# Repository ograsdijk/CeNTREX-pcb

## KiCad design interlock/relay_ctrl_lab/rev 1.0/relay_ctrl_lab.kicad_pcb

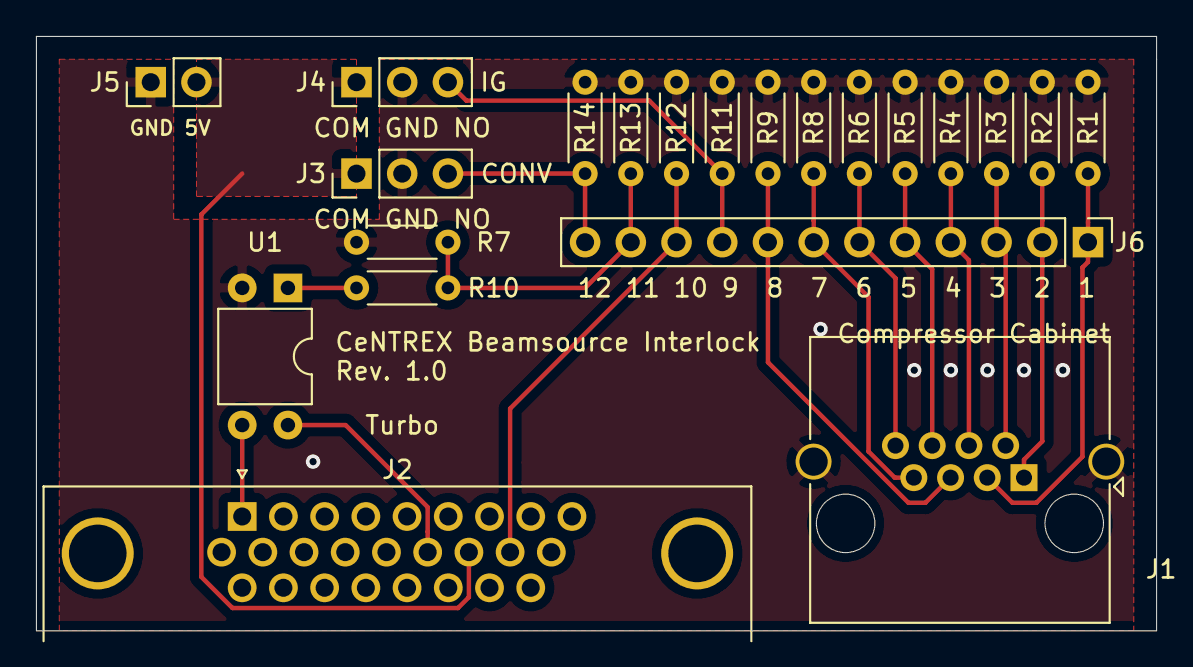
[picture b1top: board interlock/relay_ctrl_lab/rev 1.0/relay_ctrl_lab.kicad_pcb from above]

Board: 2 copper layers, 62.2 x 33.0 mm, 21 parts (0 on the bottom side), 17 nets.

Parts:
J1: RJ45_Shielded; RJ45_Amphenol_RJHSE5380
J2: Conn_01x26; DSUB-26-HD_Male_Horizontal_P2.29x1.98mm_EdgePinOffset3.03mm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
J3, J4: Conn_01x03; PinHeader_1x03_P2.54mm_Vertical
J5: Conn_01x02; PinHeader_1x02_P2.54mm_Vertical
J6: Conn_01x12; PinHeader_1x12_P2.54mm_Vertical
R1, R2, R3, R4, R5, R6, R8, R9, R11, R12, R13, R14: R; R_Axial_DIN0204_L3.6mm_D1.6mm_P5.08mm_Horizontal
R7: 10k; R_Axial_DIN0204_L3.6mm_D1.6mm_P5.08mm_Horizontal
R10: 1.2k; R_Axial_DIN0204_L3.6mm_D1.6mm_P5.08mm_Horizontal
U1: TLP222A; DIP-4_W7.62mm

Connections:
+5V: J2.16, J3.1, J4.1, J5.2
Backing1_active: J1.3, J6.1, R1.1
Backing1_interlock: J1.7, J6.7, R8.1
Backing2_active: J1.4, J6.4, R4.1
Backing2_interlock: J1.8, J6.6, R6.1
Compressor1_active: J1.1, J6.2, R2.1
Compressor1_interlock: J1.5, J6.8, R9.1
Compressor2_active: J1.2, J6.3, R3.1
Compressor2_interlock: J1.6, J6.5, R5.1
Convection_relay: J3.3, J6.12, R14.1
GND: J1.SH, J3.2, J4.2, J5.1, R1.2, R2.2, R3.2, R4.2, R5.2, R6.2, R7.2, R8.2, R9.2, R11.2, R12.2, R13.2, R14.2, U1.2
IG_relay: J4.3, J6.9, R11.1
unnamed: R10.2, U1.1
Turbo_Vref: J2.1, U1.3
Turbo_active: J2.17, J6.10, R12.1
Turbo_interlock: J6.11, R7.1, R10.1, R13.1
Turbo_remotepriority: J2.15, U1.4

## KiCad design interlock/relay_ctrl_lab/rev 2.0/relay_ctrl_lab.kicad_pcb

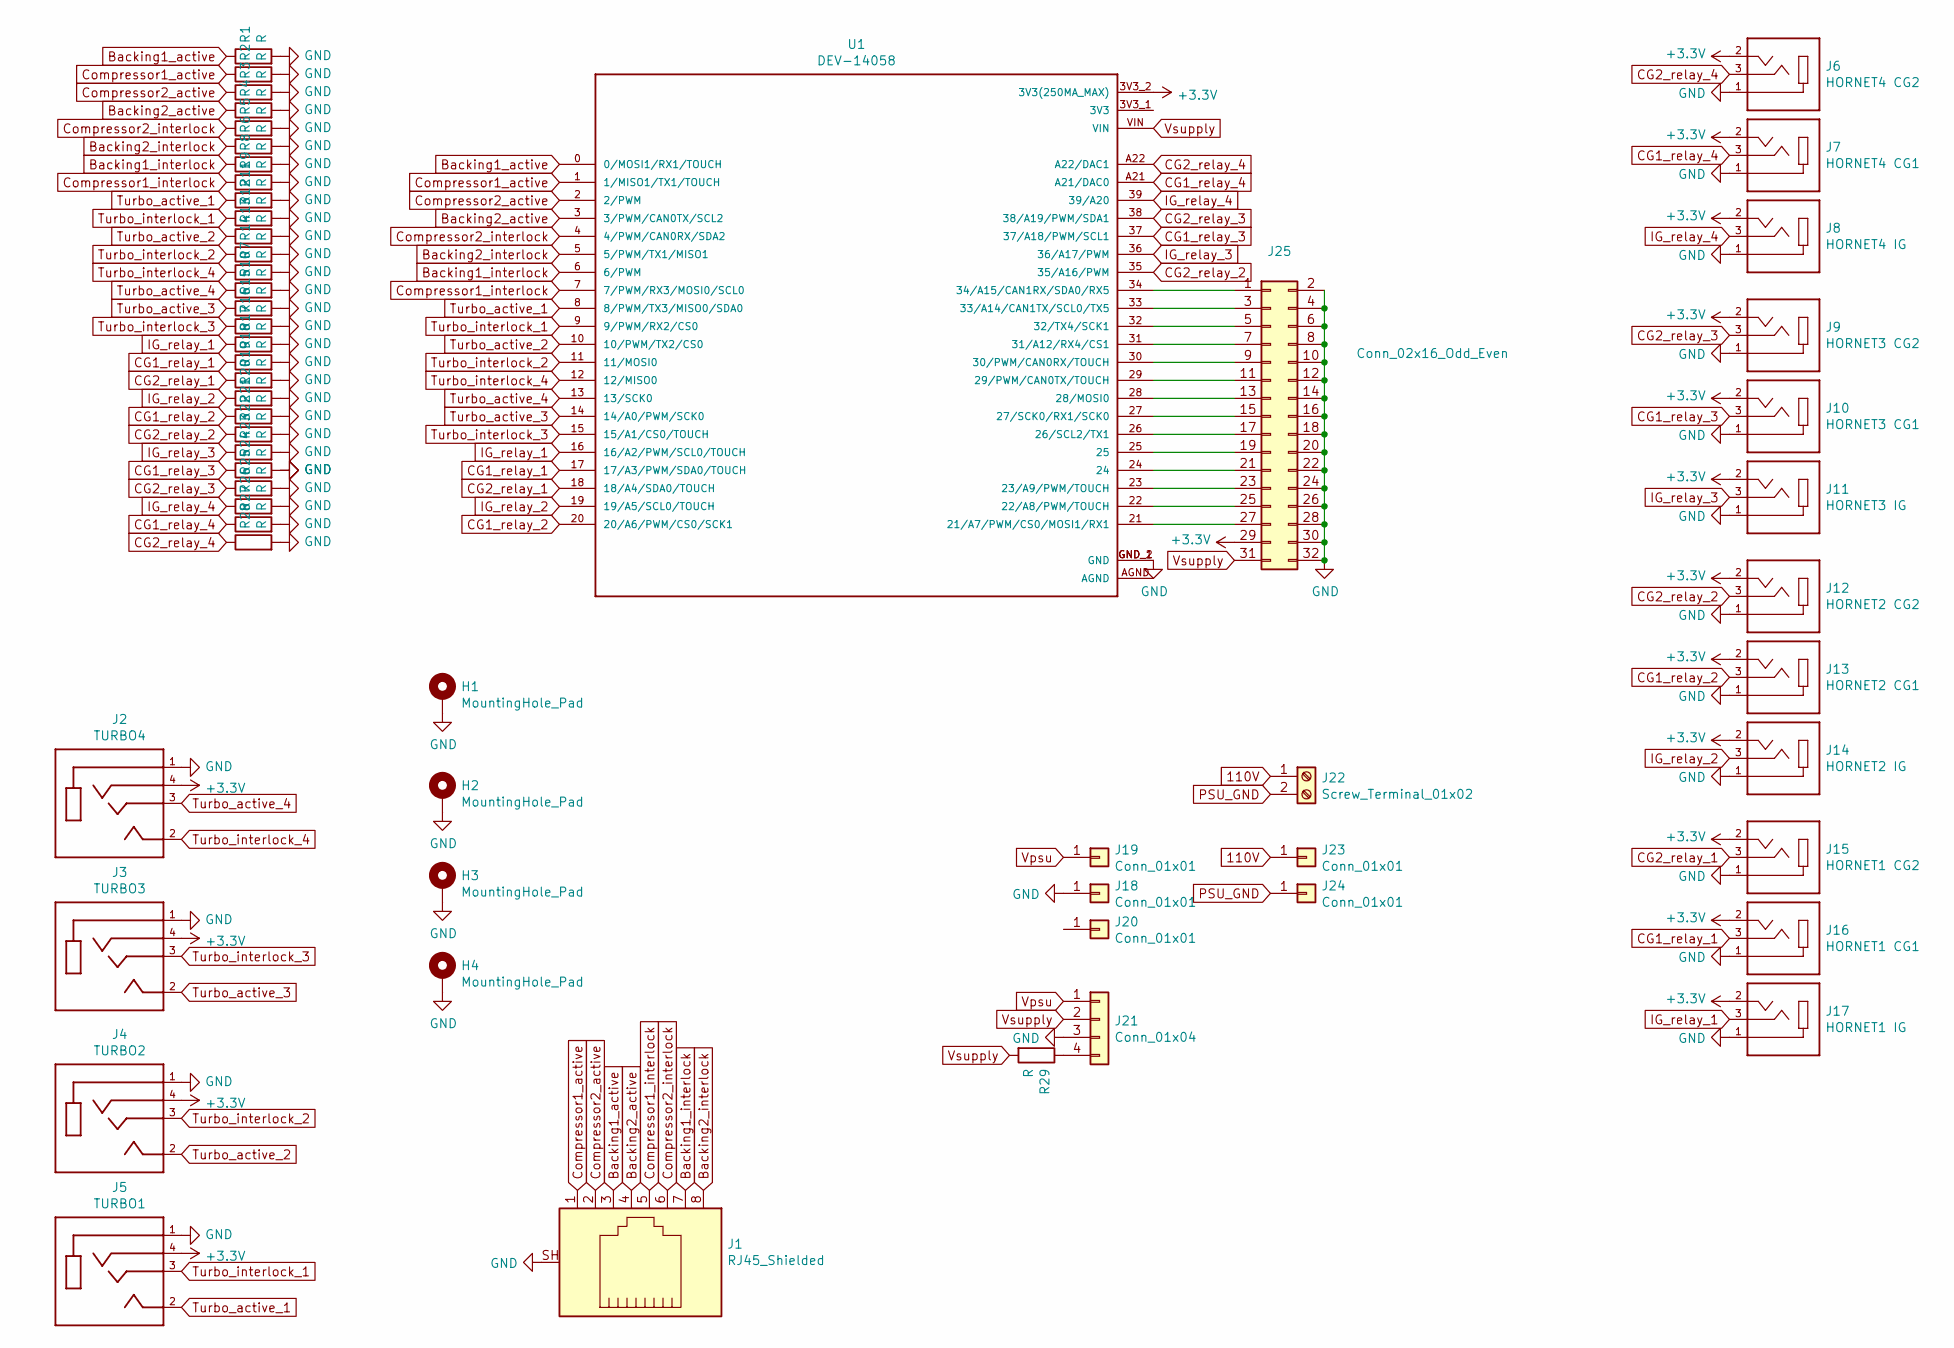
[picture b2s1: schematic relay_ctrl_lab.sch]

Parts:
H1, H2, H3, H4: MountingHole_Pad; MountingHole_3.2mm_M3_DIN965_Pad
J1: RJ45_Shielded; RJ45_Amphenol_RJHSE5380
J2: TURBO4; CUI_SJ-43514-SMT
J3: TURBO3; CUI_SJ-43514-SMT
J4: TURBO2; CUI_SJ-43514-SMT
J5: TURBO1; CUI_SJ-43514-SMT
J6: HORNET4 CG2; CUI_SJ-3523-SMT-TR
J7: HORNET4 CG1; CUI_SJ-3523-SMT-TR
J8: HORNET4 IG; CUI_SJ-3523-SMT-TR
J9: HORNET3 CG2; CUI_SJ-3523-SMT-TR
J10: HORNET3 CG1; CUI_SJ-3523-SMT-TR
J11: HORNET3 IG; CUI_SJ-3523-SMT-TR
J12: HORNET2 CG2; CUI_SJ-3523-SMT-TR
J13: HORNET2 CG1; CUI_SJ-3523-SMT-TR
J14: HORNET2 IG; CUI_SJ-3523-SMT-TR
J15: HORNET1 CG2; CUI_SJ-3523-SMT-TR
J16: HORNET1 CG1; CUI_SJ-3523-SMT-TR
J17: HORNET1 IG; CUI_SJ-3523-SMT-TR
J18, J19, J20, J23, J24: Conn_01x01; PinHeader_1x01_P2.54mm_Vertical
J21: Conn_01x04; PinHeader_1x04_P2.54mm_Vertical
J22: Screw_Terminal_01x02; TerminalBlock_RND_205-00001_1x02_P5.00mm_Horizontal
J25: Conn_02x16_Odd_Even; PinHeader_2x16_P2.54mm_Vertical
R1, R2, R3, R4, R5, R6, R7, R8, R9, R10, R11, R12, R13, R14, R15, R16, R17, R18, R19, R20, R21, R22, R23, R24, R25, R26, R27, R28, R29: R; R_Axial_DIN0204_L3.6mm_D1.6mm_P5.08mm_Horizontal
U1: DEV-14058; SPARKFUN_DEV-14058

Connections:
110V: J22.1, J23.1
+3V3: J2.4 (RING2), J3.4 (RING2), J4.4 (RING2), J5.4 (RING2), J6.2, J7.2, J8.2, J9.2, J10.2, J11.2, J12.2, J13.2, J14.2, J15.2, J16.2, J17.2, J25.29, U1.3V3_2 (3V3(250MA_MAX))
Backing1_active: J1.3, R1.1, U1.0 (0/MOSI1/RX1/TOUCH)
Backing1_interlock: J1.7, R8.1, U1.6 (6/PWM)
Backing2_active: J1.4, R4.1, U1.3 (3/PWM/CAN0TX/SCL2)
Backing2_interlock: J1.8, R6.1, U1.5 (5/PWM/TX1/MISO1)
CG1_relay_1: J16.3, R18.1, U1.17 (17/A3/PWM/SDA0/TOUCH)
CG1_relay_2: J13.3, R21.1, U1.20 (20/A6/PWM/CS0/SCK1)
CG1_relay_3: J10.3, R24.1, U1.37 (37/A18/PWM/SCL1)
CG1_relay_4: J7.3, R27.1, U1.A21 (A21/DAC0)
CG2_relay_1: J15.3, R19.1, U1.18 (18/A4/SDA0/TOUCH)
CG2_relay_2: J12.3, R22.1, U1.35 (35/A16/PWM)
CG2_relay_3: J9.3, R25.1, U1.38 (38/A19/PWM/SDA1)
CG2_relay_4: J6.3, R28.1, U1.A22 (A22/DAC1)
Compressor1_active: J1.1, R2.1, U1.1 (1/MISO1/TX1/TOUCH)
Compressor1_interlock: J1.5, R9.1, U1.7 (7/PWM/RX3/MOSI0/SCL0)
Compressor2_active: J1.2, R3.1, U1.2 (2/PWM)
Compressor2_interlock: J1.6, R5.1, U1.4 (4/PWM/CAN0RX/SDA2)
GND: H1.1, H2.1, H3.1, H4.1, J1.SH, J2.1 (SLEEVE), J3.1 (SLEEVE), J4.1 (SLEEVE), J5.1 (SLEEVE), J6.1, J7.1, J8.1, J9.1, J10.1, J11.1, J12.1, J13.1, J14.1, J15.1, J16.1, J17.1, J18.1, J21.3, J25.2, J25.4, J25.6, J25.8, J25.10, J25.12, J25.14, J25.16, J25.18, J25.20, J25.22, J25.24, J25.26, J25.28, J25.30, J25.32, R1.2, R2.2, R3.2, R4.2, R5.2, R6.2, R7.2, R8.2, R9.2, R10.2, R11.2, R12.2, R13.2, R14.2, R15.2, R16.2, R17.2, R18.2, R19.2, R20.2, R21.2, R22.2, R23.2, R24.2, R25.2, R26.2, R27.2, R28.2, U1.GND_1 (GND), U1.GND_2 (GND)
IG_relay_1: J17.3, R17.1, U1.16 (16/A2/PWM/SCL0/TOUCH)
IG_relay_2: J14.3, R20.1, U1.19 (19/A5/SCL0/TOUCH)
IG_relay_3: J11.3, R23.1, U1.36 (36/A17/PWM)
IG_relay_4: J8.3, R26.1, U1.39 (39/A20)
unnamed: J21.4, R29.1
unnamed: J25.1, U1.34 (34/A15/CAN1RX/SDA0/RX5)
unnamed: J25.3, U1.33 (33/A14/CAN1TX/SCL0/TX5)
unnamed: J25.5, U1.32 (32/TX4/SCK1)
unnamed: J25.7, U1.31 (31/A12/RX4/CS1)
unnamed: J25.9, U1.30 (30/PWM/CAN0RX/TOUCH)
unnamed: J25.11, U1.29 (29/PWM/CAN0TX/TOUCH)
unnamed: J25.13, U1.28 (28/MOSI0)
unnamed: J25.15, U1.27 (27/SCK0/RX1/SCK0)
unnamed: J25.17, U1.26 (26/SCL2/TX1)
unnamed: J25.19, U1.25
unnamed: J25.21, U1.24
unnamed: J25.23, U1.23 (23/A9/PWM/TOUCH)
unnamed: J25.25, U1.22 (22/A8/PWM/TOUCH)
unnamed: J25.27, U1.21 (21/A7/PWM/CS0/MOSI1/RX1)
PSU_GND: J22.2, J24.1
Turbo_active_1: J5.2 (TIP), R11.1, U1.8 (8/PWM/TX3/MISO0/SDA0)
Turbo_active_2: J4.2 (TIP), R13.1, U1.10 (10/PWM/TX2/CS0)
Turbo_active_3: J3.2 (TIP), R15.1, U1.14 (14/A0/PWM/SCK0)
Turbo_active_4: J2.3 (RING1), R10.1, U1.13 (13/SCK0)
Turbo_interlock_1: J5.3 (RING1), R12.1, U1.9 (9/PWM/RX2/CS0)
Turbo_interlock_2: J4.3 (RING1), R14.1, U1.11 (11/MOSI0)
Turbo_interlock_3: J3.3 (RING1), R16.1, U1.15 (15/A1/CS0/TOUCH)
Turbo_interlock_4: J2.2 (TIP), R7.1, U1.12 (12/MISO0)
Vpsu: J19.1, J21.1
Vsupply: J21.2, J25.31, R29.2, U1.VIN

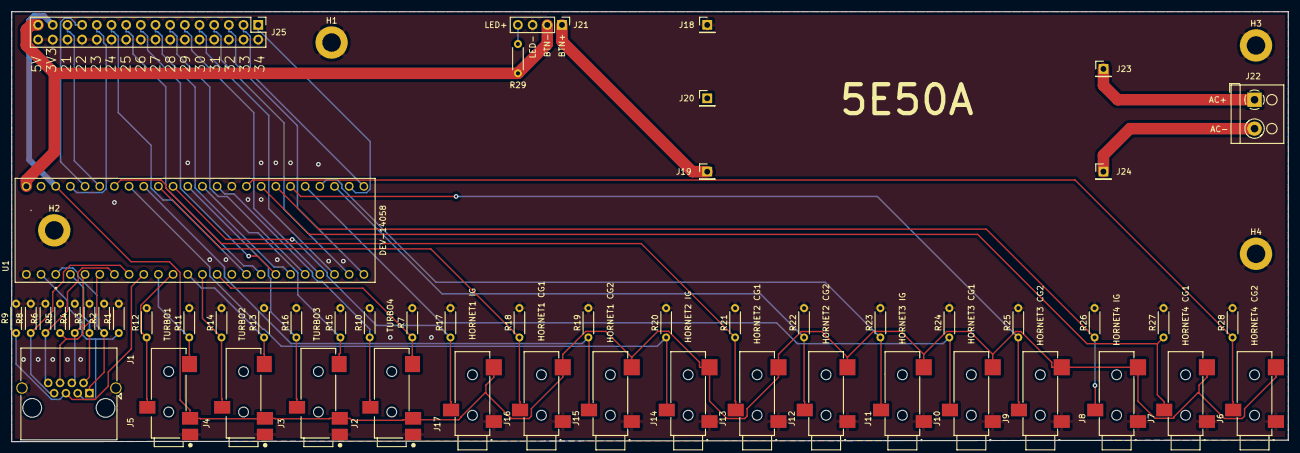
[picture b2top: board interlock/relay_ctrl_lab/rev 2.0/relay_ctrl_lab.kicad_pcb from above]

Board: 2 copper layers, 221.0 x 74.4 mm, 59 parts (0 on the bottom side), 49 nets.

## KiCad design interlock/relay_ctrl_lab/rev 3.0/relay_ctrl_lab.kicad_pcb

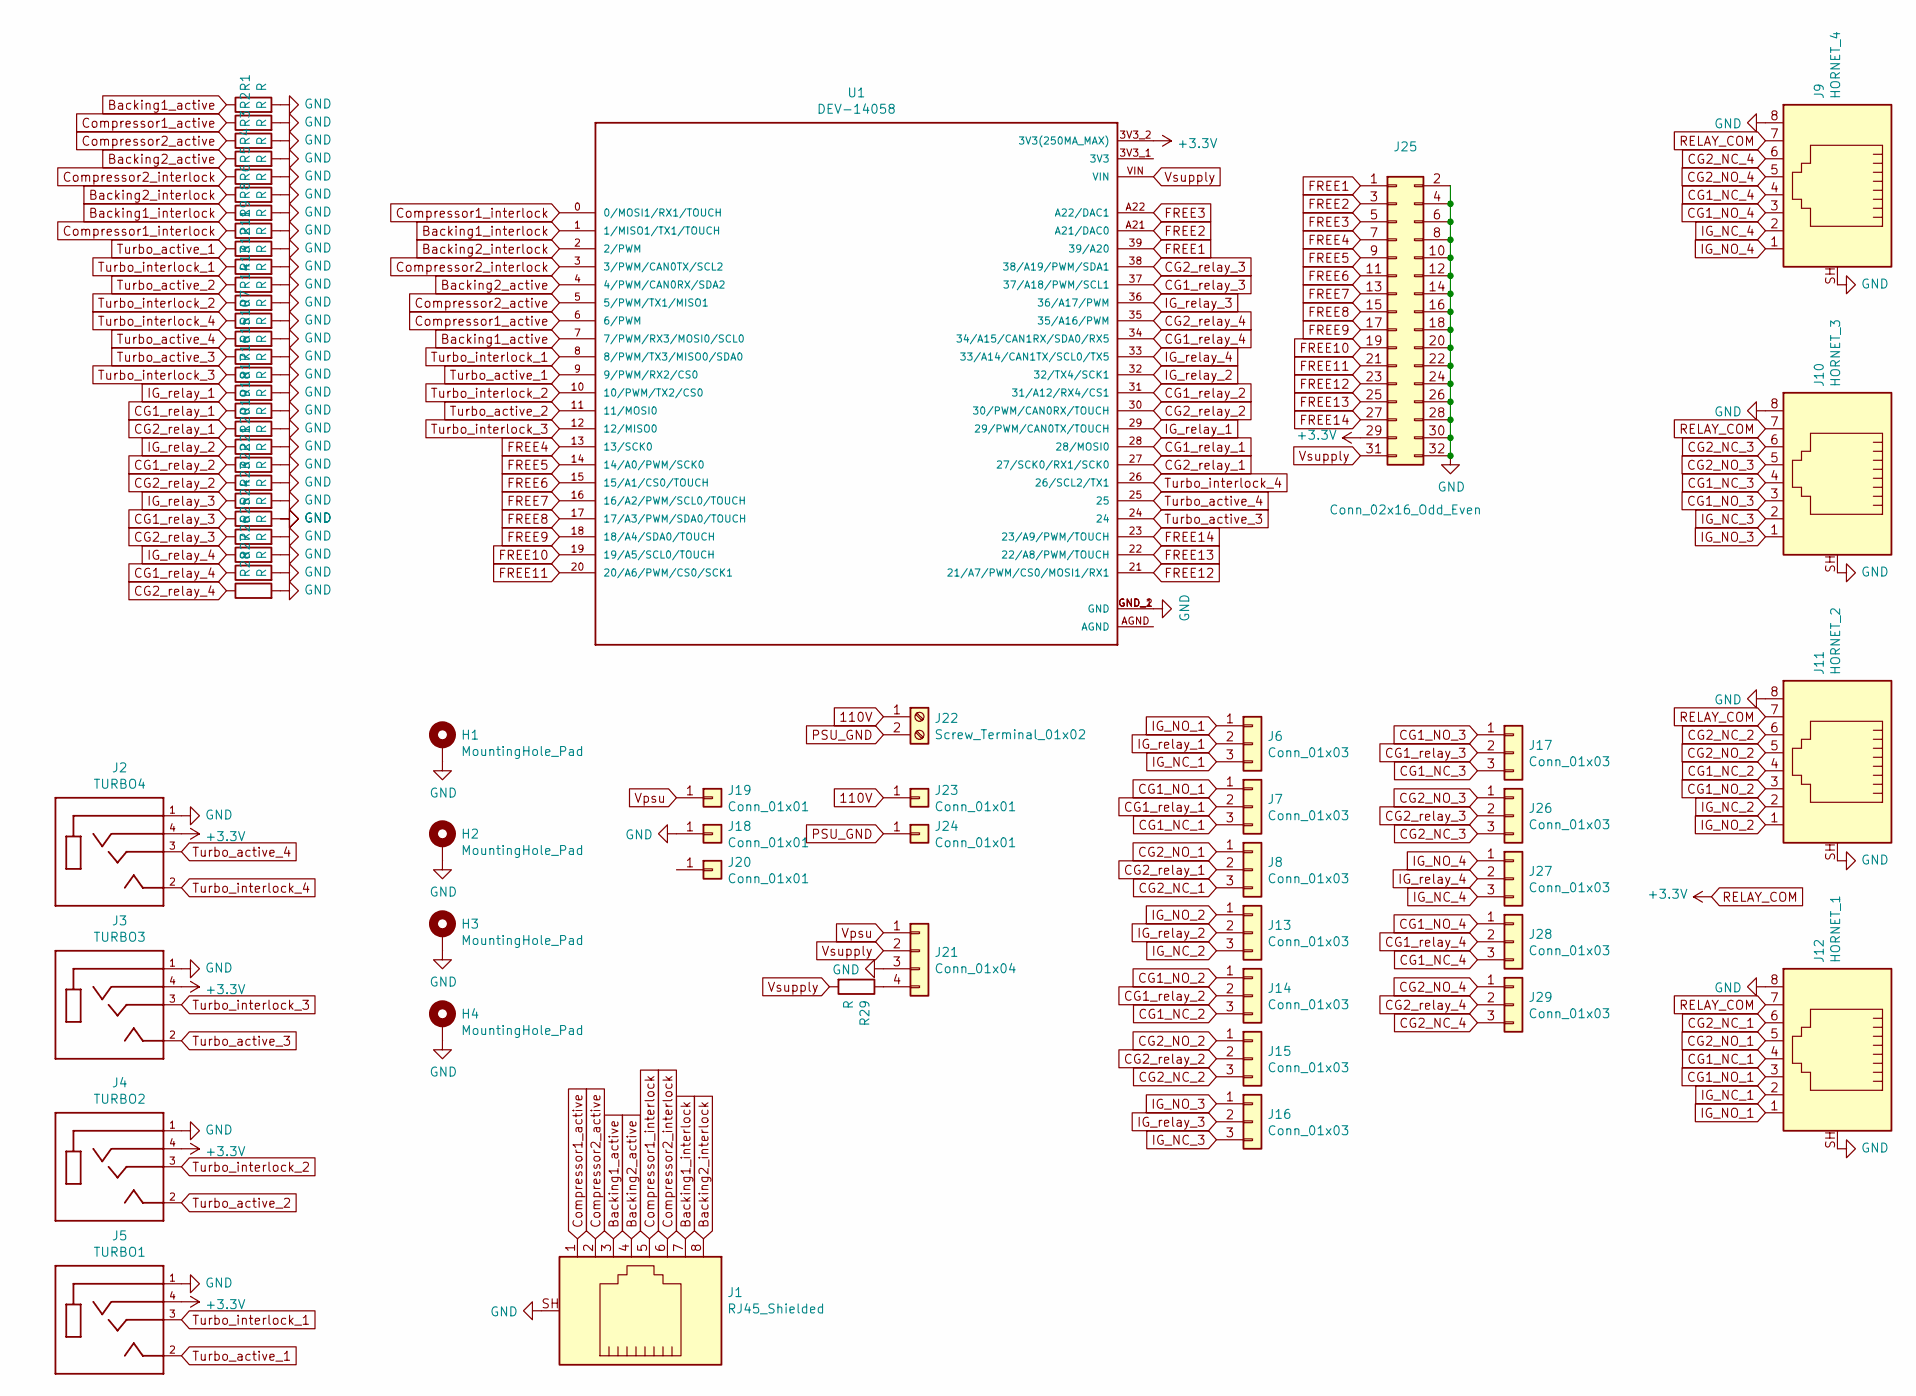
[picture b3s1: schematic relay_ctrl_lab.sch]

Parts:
H1, H2, H3, H4: MountingHole_Pad; MountingHole_3.2mm_M3_DIN965_Pad
J1: RJ45_Shielded; RJ45_Amphenol_RJHSE5380
J2: TURBO4; CUI_SJ-43514-SMT
J3: TURBO3; CUI_SJ-43514-SMT
J4: TURBO2; CUI_SJ-43514-SMT
J5: TURBO1; CUI_SJ-43514-SMT
J6, J7, J8, J13, J14, J15, J16, J17, J26, J27, J28, J29: Conn_01x03; PinHeader_1x03_P2.54mm_Vertical
J9: HORNET_4; RJ45_Amphenol_RJHSE5380
J10: HORNET_3; RJ45_Amphenol_RJHSE5380
J11: HORNET_2; RJ45_Amphenol_RJHSE5380
J12: HORNET_1; RJ45_Amphenol_RJHSE5380
J18, J19, J20, J23, J24: Conn_01x01; PinHeader_1x01_P2.54mm_Vertical
J21: Conn_01x04; PinHeader_1x04_P2.54mm_Vertical
J22: Screw_Terminal_01x02; TerminalBlock_RND_205-00001_1x02_P5.00mm_Horizontal
J25: Conn_02x16_Odd_Even; PinHeader_2x16_P2.54mm_Vertical
R1, R2, R3, R4, R5, R6, R7, R8, R9, R10, R11, R12, R13, R14, R15, R16, R17, R18, R19, R20, R21, R22, R23, R24, R25, R26, R27, R28, R29: R; R_Axial_DIN0204_L3.6mm_D1.6mm_P5.08mm_Horizontal
U1: DEV-14058; SPARKFUN_DEV-14058

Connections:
110V: J22.1, J23.1
Backing1_active: J1.3, R1.1, U1.7 (7/PWM/RX3/MOSI0/SCL0)
Backing1_interlock: J1.7, R8.1, U1.1 (1/MISO1/TX1/TOUCH)
Backing2_active: J1.4, R4.1, U1.4 (4/PWM/CAN0RX/SDA2)
Backing2_interlock: J1.8, R6.1, U1.2 (2/PWM)
CG1_NC_1: J7.3, J12.4
CG1_NC_2: J11.4, J14.3
CG1_NC_3: J10.4, J17.3
CG1_NC_4: J9.4, J28.3
CG1_NO_1: J7.1, J12.3
CG1_NO_2: J11.3, J14.1
CG1_NO_3: J10.3, J17.1
CG1_NO_4: J9.3, J28.1
CG1_relay_1: J7.2, R18.1, U1.28 (28/MOSI0)
CG1_relay_2: J14.2, R21.1, U1.31 (31/A12/RX4/CS1)
CG1_relay_3: J17.2, R24.1, U1.37 (37/A18/PWM/SCL1)
CG1_relay_4: J28.2, R27.1, U1.34 (34/A15/CAN1RX/SDA0/RX5)
CG2_NC_1: J8.3, J12.6
CG2_NC_2: J11.6, J15.3
CG2_NC_3: J10.6, J26.3
CG2_NC_4: J9.6, J29.3
CG2_NO_1: J8.1, J12.5
CG2_NO_2: J11.5, J15.1
CG2_NO_3: J10.5, J26.1
CG2_NO_4: J9.5, J29.1
CG2_relay_1: J8.2, R19.1, U1.27 (27/SCK0/RX1/SCK0)
CG2_relay_2: J15.2, R22.1, U1.30 (30/PWM/CAN0RX/TOUCH)
CG2_relay_3: J26.2, R25.1, U1.38 (38/A19/PWM/SDA1)
CG2_relay_4: J29.2, R28.1, U1.35 (35/A16/PWM)
Compressor1_active: J1.1, R2.1, U1.6 (6/PWM)
Compressor1_interlock: J1.5, R9.1, U1.0 (0/MOSI1/RX1/TOUCH)
Compressor2_active: J1.2, R3.1, U1.5 (5/PWM/TX1/MISO1)
Compressor2_interlock: J1.6, R5.1, U1.3 (3/PWM/CAN0TX/SCL2)
FREE1: J25.1, U1.39 (39/A20)
FREE2: J25.3, U1.A21 (A21/DAC0)
FREE3: J25.5, U1.A22 (A22/DAC1)
FREE4: J25.7, U1.13 (13/SCK0)
FREE5: J25.9, U1.14 (14/A0/PWM/SCK0)
FREE6: J25.11, U1.15 (15/A1/CS0/TOUCH)
FREE7: J25.13, U1.16 (16/A2/PWM/SCL0/TOUCH)
FREE8: J25.15, U1.17 (17/A3/PWM/SDA0/TOUCH)
FREE9: J25.17, U1.18 (18/A4/SDA0/TOUCH)
FREE10: J25.19, U1.19 (19/A5/SCL0/TOUCH)
FREE11: J25.21, U1.20 (20/A6/PWM/CS0/SCK1)
FREE12: J25.23, U1.21 (21/A7/PWM/CS0/MOSI1/RX1)
FREE13: J25.25, U1.22 (22/A8/PWM/TOUCH)
FREE14: J25.27, U1.23 (23/A9/PWM/TOUCH)
GND: H1.1, H2.1, H3.1, H4.1, J1.SH, J2.1 (SLEEVE), J3.1 (SLEEVE), J4.1 (SLEEVE), J5.1 (SLEEVE), J9.8, J9.SH, J10.8, J10.SH, J11.8, J11.SH, J12.8, J12.SH, J18.1, J21.3, J25.2, J25.4, J25.6, J25.8, J25.10, J25.12, J25.14, J25.16, J25.18, J25.20, J25.22, J25.24, J25.26, J25.28, J25.30, J25.32, R1.2, R2.2, R3.2, R4.2, R5.2, R6.2, R7.2, R8.2, R9.2, R10.2, R11.2, R12.2, R13.2, R14.2, R15.2, R16.2, R17.2, R18.2, R19.2, R20.2, R21.2, R22.2, R23.2, R24.2, R25.2, R26.2, R27.2, R28.2, U1.GND_1 (GND), U1.GND_2 (GND)
IG_NC_1: J6.3, J12.2
IG_NC_2: J11.2, J13.3
IG_NC_3: J10.2, J16.3
IG_NC_4: J9.2, J27.3
IG_NO_1: J6.1, J12.1
IG_NO_2: J11.1, J13.1
IG_NO_3: J10.1, J16.1
IG_NO_4: J9.1, J27.1
IG_relay_1: J6.2, R17.1, U1.29 (29/PWM/CAN0TX/TOUCH)
IG_relay_2: J13.2, R20.1, U1.32 (32/TX4/SCK1)
IG_relay_3: J16.2, R23.1, U1.36 (36/A17/PWM)
IG_relay_4: J27.2, R26.1, U1.33 (33/A14/CAN1TX/SCL0/TX5)
unnamed: J21.4, R29.1
PSU_GND: J22.2, J24.1
RELAY_COM: J2.4 (RING2), J3.4 (RING2), J4.4 (RING2), J5.4 (RING2), J9.7, J10.7, J11.7, J12.7, J25.29, U1.3V3_2 (3V3(250MA_MAX))
Turbo_active_1: J5.2 (TIP), R11.1, U1.9 (9/PWM/RX2/CS0)
Turbo_active_2: J4.2 (TIP), R13.1, U1.11 (11/MOSI0)
Turbo_active_3: J3.2 (TIP), R15.1, U1.24
Turbo_active_4: J2.3 (RING1), R10.1, U1.25
Turbo_interlock_1: J5.3 (RING1), R12.1, U1.8 (8/PWM/TX3/MISO0/SDA0)
Turbo_interlock_2: J4.3 (RING1), R14.1, U1.10 (10/PWM/TX2/CS0)
Turbo_interlock_3: J3.3 (RING1), R16.1, U1.12 (12/MISO0)
Turbo_interlock_4: J2.2 (TIP), R7.1, U1.26 (26/SCL2/TX1)
Vpsu: J19.1, J21.1
Vsupply: J21.2, J25.31, R29.2, U1.VIN

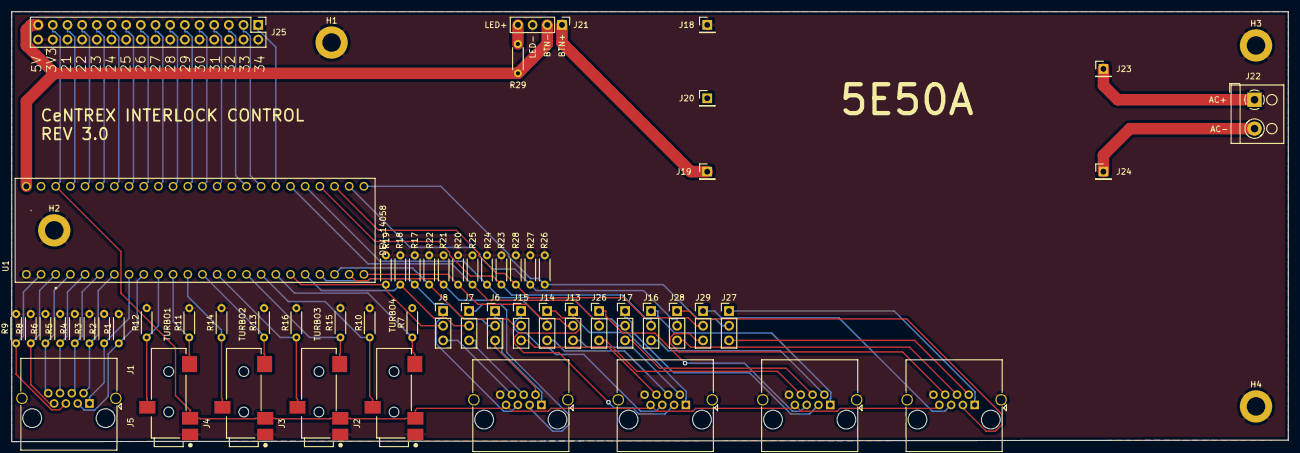
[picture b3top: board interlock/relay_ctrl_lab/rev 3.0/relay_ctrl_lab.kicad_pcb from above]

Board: 2 copper layers, 221.0 x 74.4 mm, 63 parts (0 on the bottom side), 73 nets.

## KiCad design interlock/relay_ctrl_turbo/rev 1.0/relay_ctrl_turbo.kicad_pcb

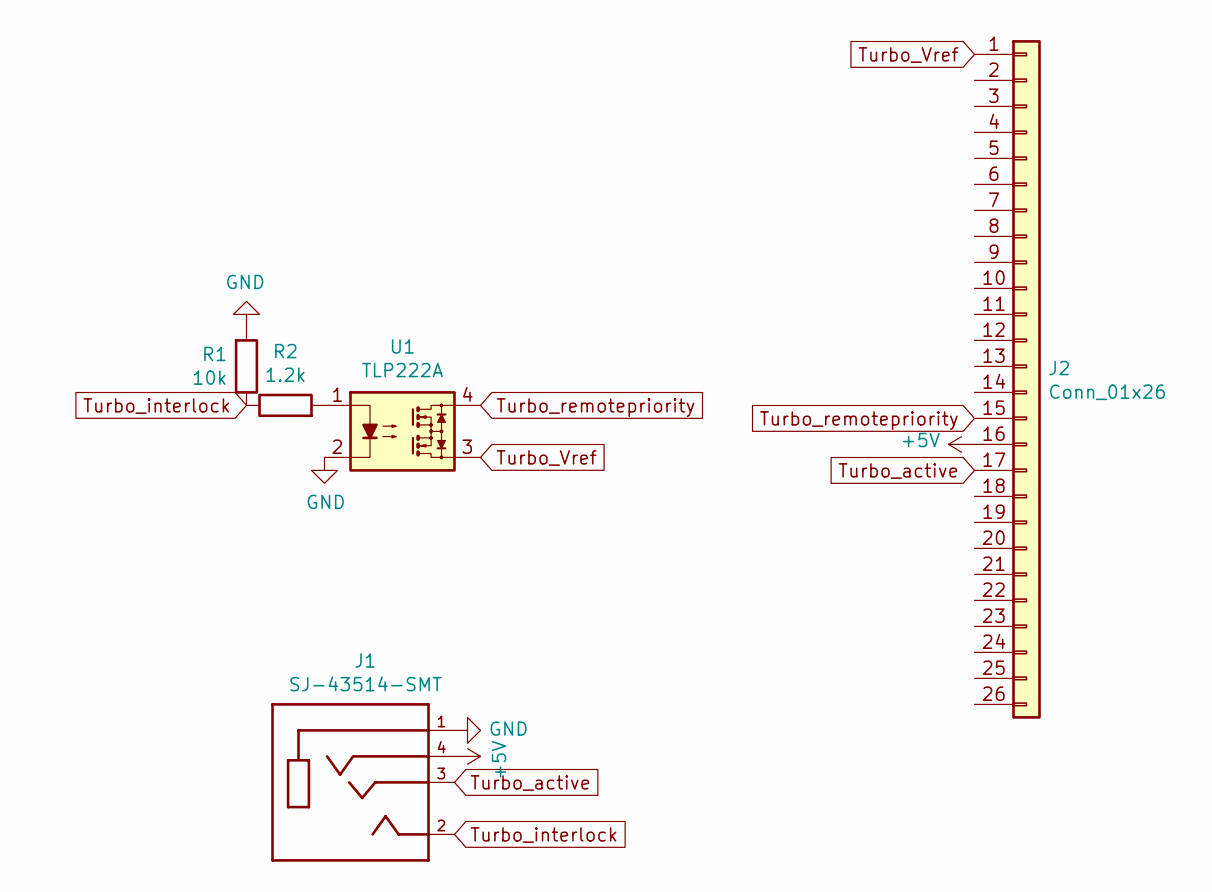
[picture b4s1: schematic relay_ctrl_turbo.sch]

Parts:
J1: SJ-43514-SMT; CUI_SJ-43514-SMT
J2: Conn_01x26; DSUB-26-HD_Male_Horizontal_P2.29x1.98mm_EdgePinOffset3.03mm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
R1: 10k; R_Axial_DIN0204_L3.6mm_D1.6mm_P5.08mm_Vertical
R2: 1.2k; R_Axial_DIN0204_L3.6mm_D1.6mm_P5.08mm_Vertical
U1: TLP222A; DIP-4_W7.62mm

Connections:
+5V: J1.4 (RING2), J2.16
GND: J1.1 (SLEEVE), R1.2, U1.2
unnamed: R2.2, U1.1
Turbo_Vref: J2.1, U1.3
Turbo_active: J1.3 (RING1), J2.17
Turbo_interlock: J1.2 (TIP), R1.1, R2.1
Turbo_remotepriority: J2.15, U1.4

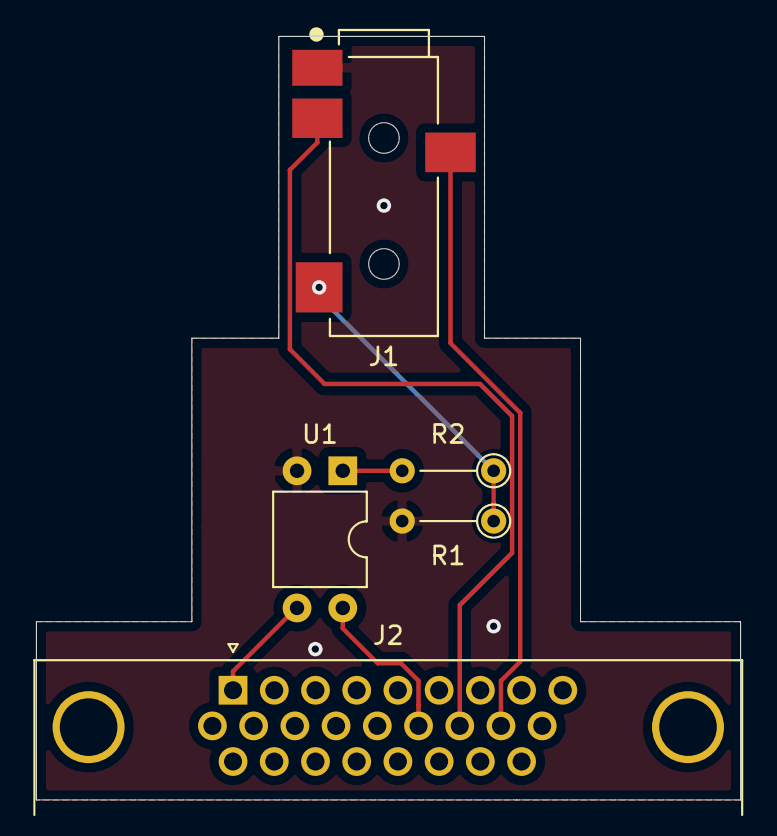
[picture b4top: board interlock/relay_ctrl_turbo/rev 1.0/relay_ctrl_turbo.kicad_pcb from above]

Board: 2 copper layers, 39.1 x 42.4 mm, 5 parts (0 on the bottom side), 7 nets.

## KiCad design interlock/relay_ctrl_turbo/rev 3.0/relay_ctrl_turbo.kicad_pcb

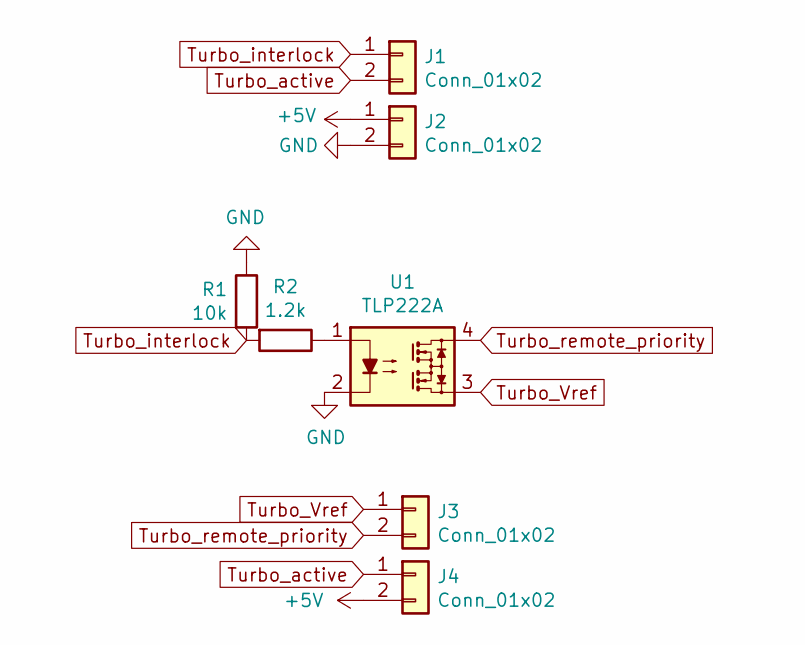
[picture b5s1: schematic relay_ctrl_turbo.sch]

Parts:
J1, J2, J3, J4: Conn_01x02; PinHeader_1x02_P2.54mm_Vertical
R1: 10k; R_Axial_DIN0204_L3.6mm_D1.6mm_P5.08mm_Horizontal
R2: 1.2k; R_Axial_DIN0204_L3.6mm_D1.6mm_P5.08mm_Horizontal
U1: TLP222A; DIP-4_W7.62mm

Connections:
+5V: J2.1, J4.2
GND: J2.2, R1.1, U1.2
unnamed: R2.1, U1.1
Turbo_Vref: J3.1, U1.3
Turbo_active: J1.2, J4.1
Turbo_interlock: J1.1, R1.2, R2.2
Turbo_remote_priority: J3.2, U1.4

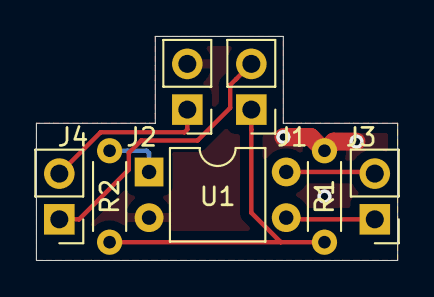
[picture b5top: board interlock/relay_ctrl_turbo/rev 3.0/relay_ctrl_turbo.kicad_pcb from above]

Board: 2 copper layers, 20.1 x 12.4 mm, 7 parts (0 on the bottom side), 7 nets.

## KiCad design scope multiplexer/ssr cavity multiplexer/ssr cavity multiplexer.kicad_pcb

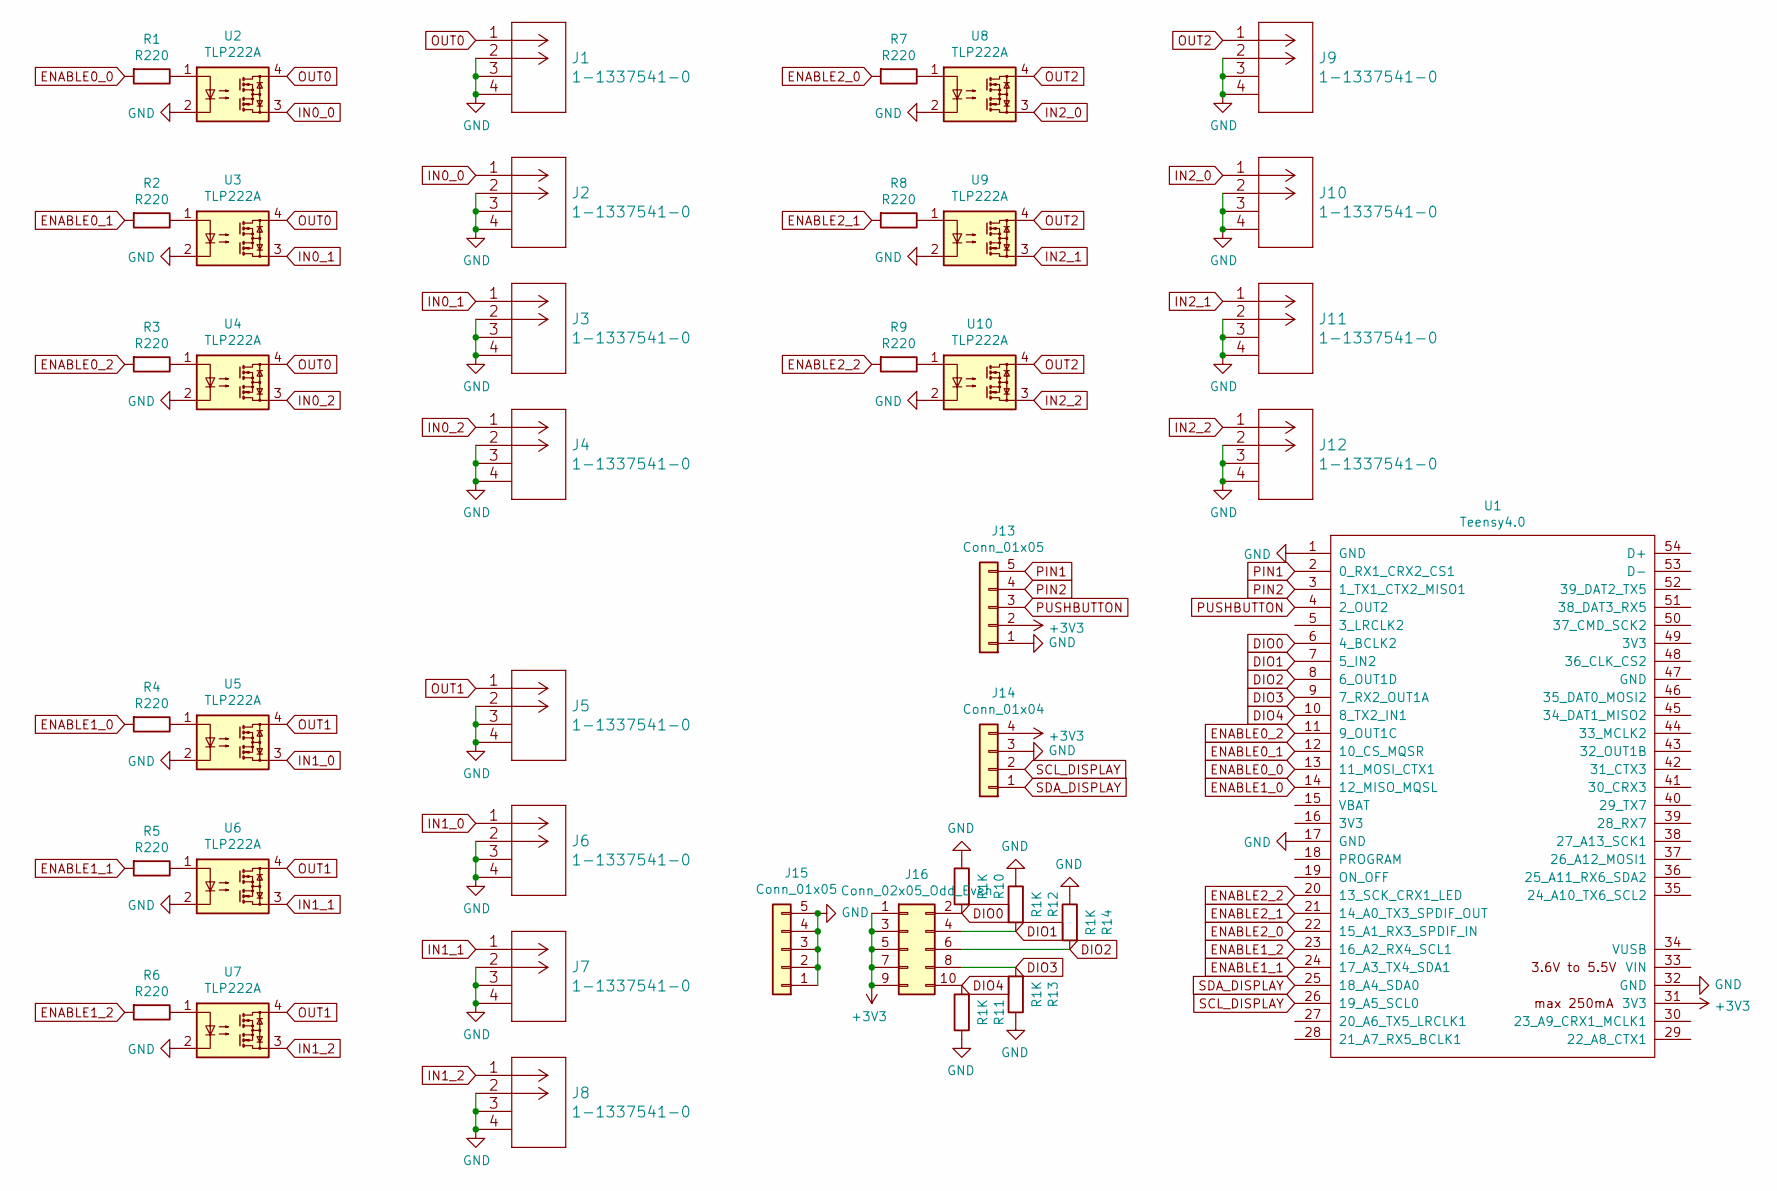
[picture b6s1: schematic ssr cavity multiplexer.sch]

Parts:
J1, J2, J3, J4, J5, J6, J7, J8, J9, J10, J11, J12: 1-1337541-0
J13, J15: Conn_01x05; PinHeader_1x05_P2.54mm_Vertical
J14: Conn_01x04; PinHeader_1x04_P2.54mm_Vertical
J16: Conn_02x05_Odd_Even; PinHeader_2x05_P2.54mm_Vertical
R1, R2, R3, R4, R5, R6, R7, R8, R9: R220; R_0805_2012Metric
R10, R11, R12, R13, R14: R1K; R_0805_2012Metric
U1: Teensy4.0; Teensy40
U2, U3, U4, U5, U6, U7, U8, U9, U10: TLP222A; DIP-4_W7.62mm

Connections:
+3V3: J13.2, J14.4, J16.1, J16.3, J16.5, J16.7, J16.9, U1.31 (3V3)
DIO0: J16.2, R10.2, U1.6 (4_BCLK2)
DIO1: J16.4, R12.2, U1.7 (5_IN2)
DIO2: J16.6, R14.2, U1.8 (6_OUT1D)
DIO3: J16.8, R13.2, U1.9 (7_RX2_OUT1A)
DIO4: J16.10, R11.2, U1.10 (8_TX2_IN1)
ENABLE0_0: R1.2, U1.13 (11_MOSI_CTX1)
ENABLE0_1: R2.2, U1.12 (10_CS_MQSR)
ENABLE0_2: R3.2, U1.11 (9_OUT1C)
ENABLE1_0: R4.2, U1.14 (12_MISO_MQSL)
ENABLE1_1: R5.2, U1.24 (17_A3_TX4_SDA1)
ENABLE1_2: R6.2, U1.23 (16_A2_RX4_SCL1)
ENABLE2_0: R7.2, U1.22 (15_A1_RX3_SPDIF_IN)
ENABLE2_1: R8.2, U1.21 (14_A0_TX3_SPDIF_OUT)
ENABLE2_2: R9.2, U1.20 (13_SCK_CRX1_LED)
GND: J1.2, J1.3 (SHIELD), J1.4 (SHIELD), J2.2, J2.3 (SHIELD), J2.4 (SHIELD), J3.2, J3.3 (SHIELD), J3.4 (SHIELD), J4.2, J4.3 (SHIELD), J4.4 (SHIELD), J5.2, J5.3 (SHIELD), J5.4 (SHIELD), J6.2, J6.3 (SHIELD), J6.4 (SHIELD), J7.2, J7.3 (SHIELD), J7.4 (SHIELD), J8.2, J8.3 (SHIELD), J8.4 (SHIELD), J9.2, J9.3 (SHIELD), J9.4 (SHIELD), J10.2, J10.3 (SHIELD), J10.4 (SHIELD), J11.2, J11.3 (SHIELD), J11.4 (SHIELD), J12.2, J12.3 (SHIELD), J12.4 (SHIELD), J13.1, J14.3, J15.1, J15.2, J15.3, J15.4, J15.5, R10.1, R11.1, R12.1, R13.1, R14.1, U1.1 (GND), U1.17 (GND), U1.32 (GND), U2.2, U3.2, U4.2, U5.2, U6.2, U7.2, U8.2, U9.2, U10.2
IN0_0: J2.1, U2.3
IN0_1: J3.1, U3.3
IN0_2: J4.1, U4.3
IN1_0: J6.1, U5.3
IN1_1: J7.1, U6.3
IN1_2: J8.1, U7.3
IN2_0: J10.1, U8.3
IN2_1: J11.1, U9.3
IN2_2: J12.1, U10.3
unnamed: R1.1, U2.1
unnamed: R2.1, U3.1
unnamed: R3.1, U4.1
unnamed: R4.1, U5.1
unnamed: R5.1, U6.1
unnamed: R6.1, U7.1
unnamed: R7.1, U8.1
unnamed: R8.1, U9.1
unnamed: R9.1, U10.1
OUT0: J1.1, U2.4, U3.4, U4.4
OUT1: J5.1, U5.4, U6.4, U7.4
OUT2: J9.1, U8.4, U9.4, U10.4
PIN1: J13.5, U1.2 (0_RX1_CRX2_CS1)
PIN2: J13.4, U1.3 (1_TX1_CTX2_MISO1)
PUSHBUTTON: J13.3, U1.4 (2_OUT2)
SCL_DISPLAY: J14.2, U1.26 (19_A5_SCL0)
SDA_DISPLAY: J14.1, U1.25 (18_A4_SDA0)

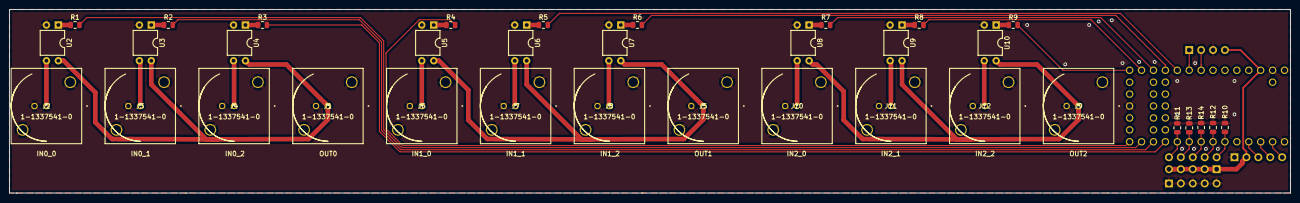
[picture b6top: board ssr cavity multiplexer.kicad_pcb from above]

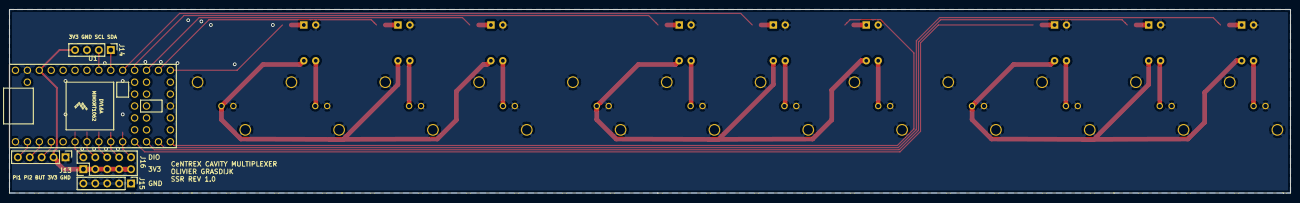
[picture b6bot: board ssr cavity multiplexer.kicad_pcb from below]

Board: 2 copper layers, 273.1 x 39.1 mm, 40 parts (5 on the bottom side), 42 nets.

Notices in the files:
parts and their libraries:
Copyright 2016 Accelerated Designs. All rights reserved.
